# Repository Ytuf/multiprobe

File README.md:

# MultiProbe Pico Debugger :lemon:

# Description
A development board to debug multiple pico devices based on the official debug probe ( https://github.com/raspberrypi/debugprobe ) which does the following:
- 4 active SWD ports, debug four targets at once using a single usb/device.
- Extra indicator LEDs displays which port is active.
- 4 UARTS multiplexed to 2 CDC Com ports.
- Supports RP2040 & RP2350 based boards.

## Compatibility
Tested on the following platforms:
- Ubuntu 22.04
- Mac mini mac OS Sequoia 15.6.1
- Windows 10 *(requires driver workaround using zadig)*

## Installation
Install VSCode and the official Raspberry Pi Pico extension ( https://marketplace.visualstudio.com/items?itemName=raspberry-pi.raspberry-pi-pico )

## SWD target
To set the debug target use the "cmsis-dap usb interface" OpenOCD command which can be set in the vscode launch.json
```
"cmsis-dap usb interface 0",            // Use DEBUG 1 port
"cmsis-dap usb interface 1",            // Use DEBUG 2 port
"cmsis-dap usb interface 2",            // Use DEBUG 3 port
"cmsis-dap usb interface 3",            // Use DEBUG 4 port
```

## Example configurations
To debug all four targets with dual UARTs add the following launch config section to each VSCode project. 
Only 2 projects can have an active UART due to the limited number of UARTs on the RP2350 and pin assignments.

Debug project 1 with UART on COM port ACM0:
```
"openOCDLaunchCommands": [    
    "adapter speed 5000",
    "cmsis-dap usb interface 0",            // Use DEBUG 1 port
    "init",                
    "cmsis-dap cmd 0x81",                   // Use UART1 on ACM0   ( HWUart0 )
]
```

Debug project 2 with UART on COM port ACM1:
```
"openOCDLaunchCommands": [    
    "adapter speed 5000",
    "cmsis-dap usb interface 1",            // Use DEBUG 2 port
    "init",                
    "cmsis-dap cmd 0x92",                   // Use UART2 on ACM1   ( HWUart1 )
]
```

Debug project 3 with no UART
```
"openOCDLaunchCommands": [    
    "adapter speed 5000",
    "cmsis-dap usb interface 2",            // Use DEBUG 3 port    
]
```

Debug project 4 with no UART
```
"openOCDLaunchCommands": [    
    "adapter speed 5000",
    "cmsis-dap usb interface 3",            // Use DEBUG 4 port    
]
```

## Uart setup
There are only 2 UART devices available so 2 of the four UARTs must be routed, this defaults to UART1 -> ACM0, and UART2 -> ACM1. 
There are also some limitation on which UARTs can be used together as the RP2350 has hard limits on which pins the UART can be assigned.
he hardware UART must be different so for example UART1 and UART3 cannot be used at the same time, in that case you will have to swap the ports.
Future versions will use a PIO based UART which resolves this restriction and/or having 4 CDC devices (see limitation).

The UARTs must be assigned to a com port using the table below:

```
UART (silkscreen)   OpenOCD code    UART Device     Hardware UART
UART1               0x81            ACM0            HWUart0
UART2               0x82            ACM0            HWUart1
UART3               0x83            ACM0            HWUart0
UART4               0x84            ACM0            HWUart1
                            
UART1               0x91            ACM1            HWUart0
UART2               0x92            ACM1            HWUart1
UART3               0x93            ACM1            HWUart0
UART4               0x94            ACM1            HWUart1
```

**Hint**: The vendor code is formatted so the first digit (8 for ACM0 or 9 for ACM1) corresponds to the COM port and the last digit (1,2,3 & 4) is the 
UART number printed on the board silkscreen.

For example if you plug a device into UART4 and want to communicated on ACM1 you would enter  "cmsis-dap cmd 0x94". Some limitation apply due to the 
pico hardware UART can only be assigned to certain pins, for example UART1 and UART3 can't be used at the same time as they share the same RP2550 hardware 
device. In the future a PIO based UART will be used to allow any gpio assignment.

The probe uses vendor codes to setup the UART must be called after the OpenOCD "init" using the following command sequence set in the launch.json:

```
"openOCDLaunchCommands": [    
    "adapter speed 5000",
    "cmsis-dap usb interface 0",            // Use DEBUG 1 port
    "init",                
    "cmsis-dap cmd 0x81",                   // Use UART3 on ACM1   ( HWUart0 )
]
```

## Windows compatibility
Windows is not currently supported out the box as some workarounds are needed to function.

To enable multiple debug multiple instances of openOCD the windows driver needs replacing as the built in WinUSB will only allow a single process to access the usb device.
A utility called zadig ( https://zadig.akeo.ie/ ) can replace the driver to allow multiple openOCD instances.

Warning: This can break your system if you select the wrong device, ensure the DAP device is selected before clicking the install button.
- Plug in the debugger into a USB port.
- download and run Zadig-2.9.exe from https://zadig.akeo.ie/ and click "Yes" on the UAC permission prompt.
- Go Options -> List All Devices
- The Device list will be populated and should have 4 CMSIS-DAP devices.
- Select "CMSIS-DAP v2 Interface (Interface 0)
- The driver input on the left should read "WinUSB", change the value on the right ( after the arrow ) to "libusbK" eg. WinUSB -> libusbK.
- Click "Install driver"
- Repeat for all 4 interfaces eg. "CMSIS-DAP v2 Interface (Interface 0), "CMSIS-DAP v2 Interface (Interface 1), "CMSIS-DAP v2 Interface (Interface 2) 
and "CMSIS-DAP v2 Interface (Interface 3)
- Reboot if needed

## Hacking
Open the project in VSCode using the "Raspberry Pi Pico" extension and compile.

## Changes from debugprobe
- VSCode based project
- hacked in multiple UARTs
- hacked in multiple port PIO DAP interfaces

## Testing
Connect a pico device to each port of the debug probe then open "testing/blink_iface0", "testing/blink_iface1", "testing/blink_iface2" and "testing/blink_iface3" 
in separate windows, Hit F5 to debug each to verify the openOCD debugger works in parallel. 

## Todo
- Fork official repo ( https://github.com/raspberrypi/debugprobe ) and make it easier to integrate upstream changes.
- PIO based UART to allow any gpio assignment and 4 active uarts without the vendor command routing.
- Resolve the 2 CDC device limit in usb descriptors/tinyusb configuration.

## Building your own
Any RP2040 or RP2350 device can be used, see multiprobe-pcb.kicad_sch for the gpio assignments or order a pcb from your favorite pcb supplier by submitting the 
hw/multiprobe-pcb/production/* files. A purchasable board is also available on tindie (https://www.tindie.com/products/picolemon/multiprobe-pico-debugger/).

### Support :zap:
- Email help@picolemon.com

Copyright (c) 2025 picoLemon

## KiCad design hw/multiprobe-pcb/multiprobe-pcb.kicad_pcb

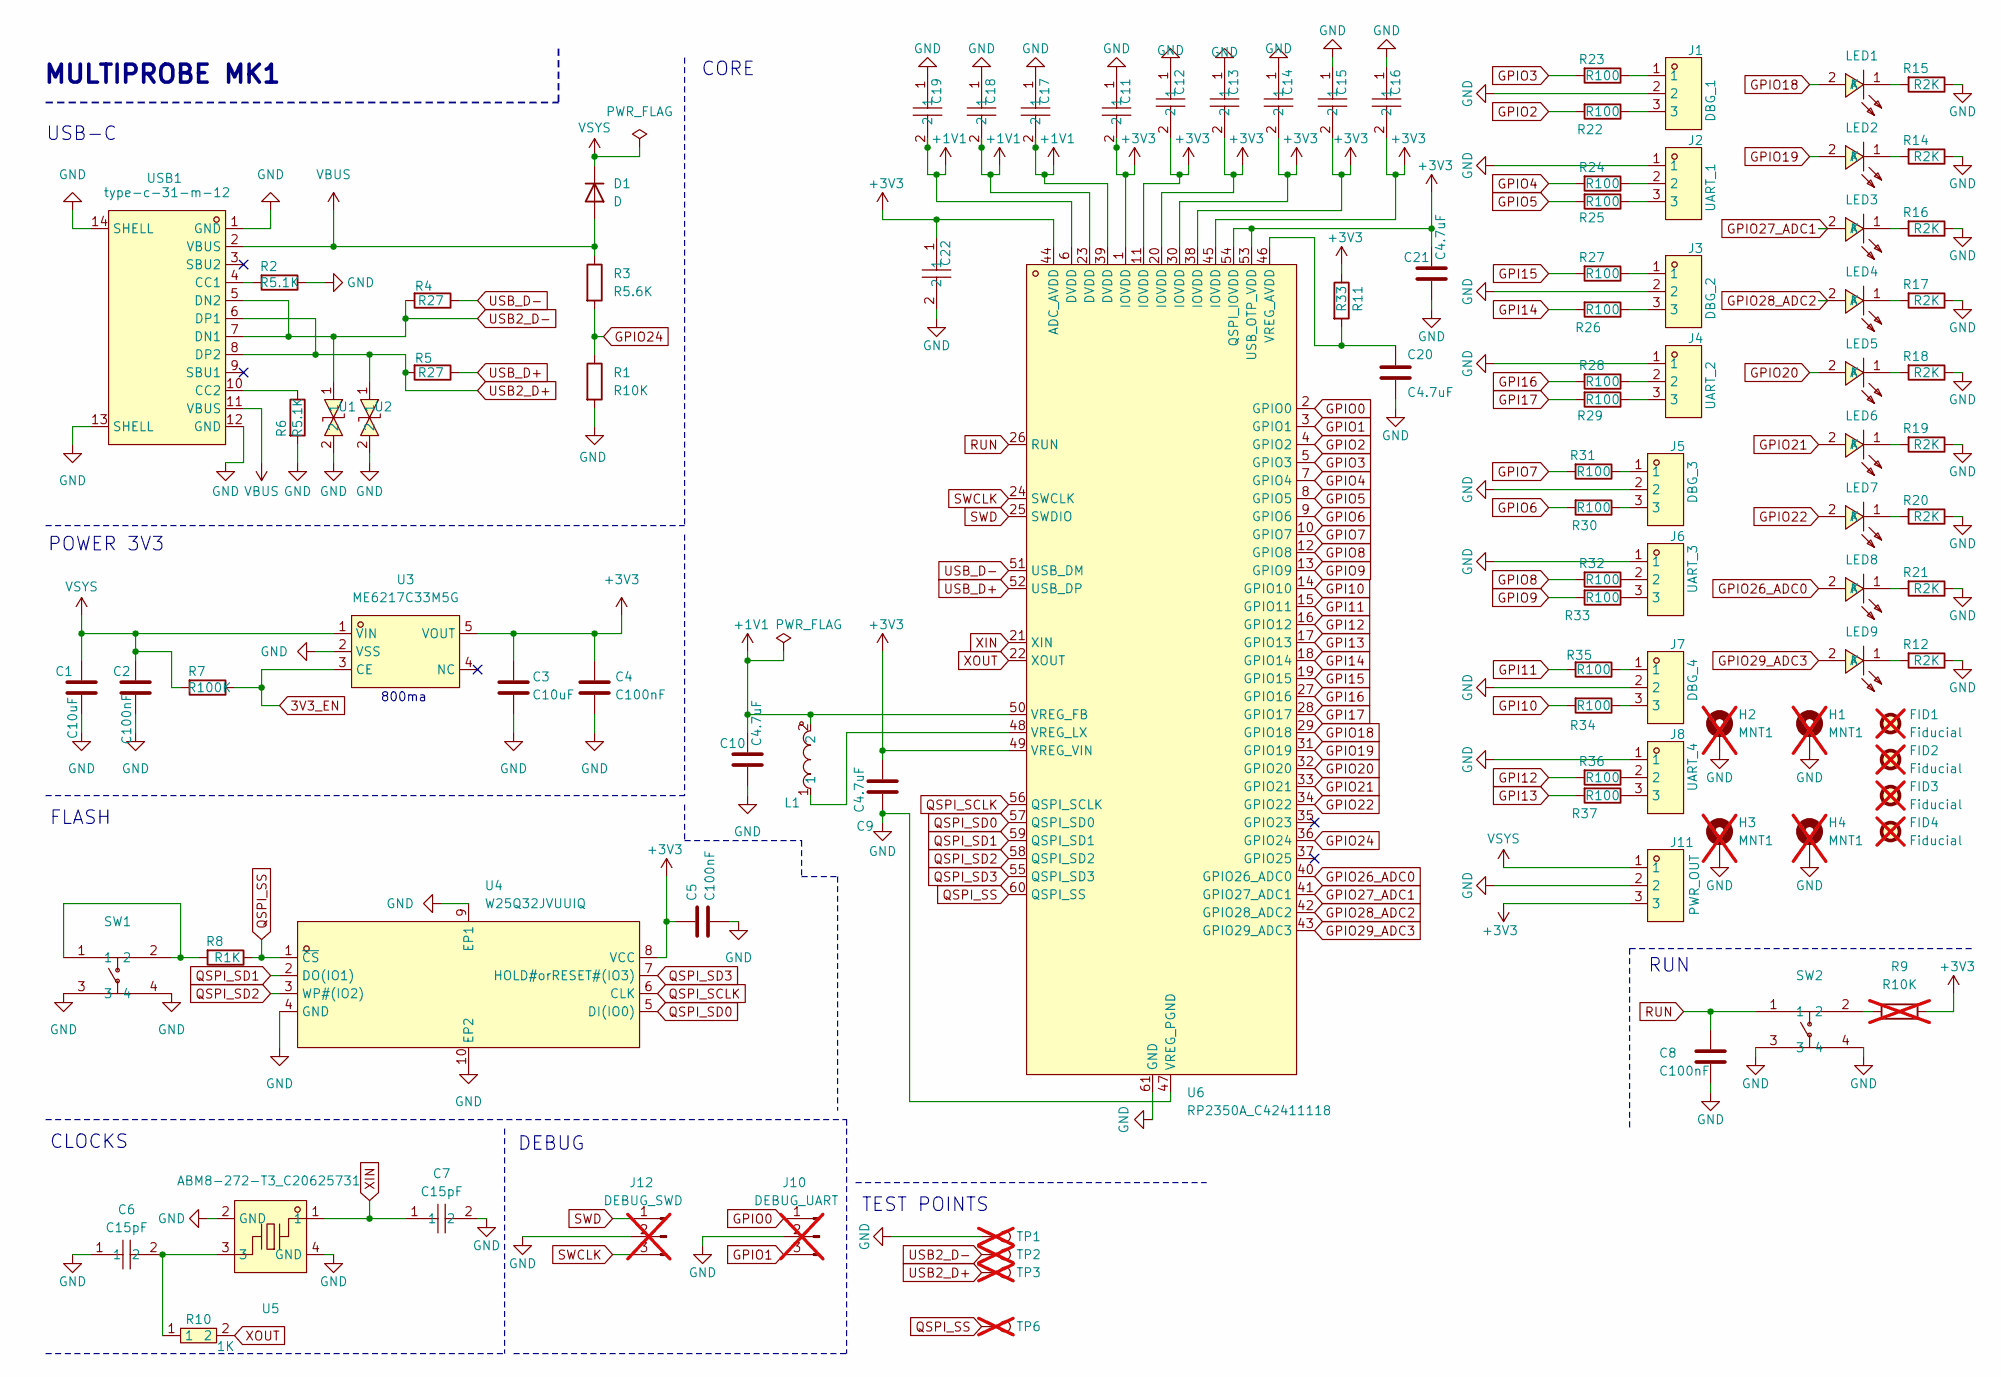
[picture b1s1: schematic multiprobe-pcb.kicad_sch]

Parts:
C1, C3: C10uF; C0402; LCSC Part C77000
C2, C4, C5, C8: C100nF; C0402; LCSC Part C77020
C6, C7: C15pF; C0402; LCSC Part C140684
C9, C10, C21: C4.7uF; C_0402_1005Metric; LCSC Part C368809
C11, C12, C13, C14, C15, C16, C17, C18, C19, C22: 100nf; C0402; LCSC Part C1525
C20: C4.7uF; C0402; LCSC Part C368809
D1: D; POWERDI-123_L2.8-W1.8-LS3.7-RD; LCSC Part C110493
FID1, FID2, FID3, FID4: Fiducial; Fiducial_1mm_Mask2mm; not fitted
H1, H2, H3, H4: MNT1; MountingHole_2.2mm_M2_DIN965_Pad; not fitted
J1: DBG_1; HDR-TH_3P-P2.54-H-M-BW7.2-P; LCSC Part C92159
J2: UART_1; HDR-TH_3P-P2.54-H-M-BW7.2-P; LCSC Part C92159
J3: DBG_2; HDR-TH_3P-P2.54-H-M-BW7.2-P; LCSC Part C92159
J4: UART_2; HDR-TH_3P-P2.54-H-M-BW7.2-P; LCSC Part C92159
J5: DBG_3; HDR-TH_3P-P2.54-H-M-BW7.2-P; LCSC Part C92159
J6: UART_3; HDR-TH_3P-P2.54-H-M-BW7.2-P; LCSC Part C92159
J7: DBG_4; HDR-TH_3P-P2.54-H-M-BW7.2-P; LCSC Part C92159
J8: UART_4; HDR-TH_3P-P2.54-H-M-BW7.2-P; LCSC Part C92159
J10: DEBUG_UART; PinHeader_1x03_P2.54mm_Vertical; not fitted
J11: PWR_OUT; HDR-TH_3P-P2.54-H-M-BW7.2-P; LCSC Part C92159
J12: DEBUG_SWD; PinHeader_1x03_P2.54mm_Vertical; not fitted
L1: AOTA-B201610S3R3-101-T; IND-SMD_L2.0-W1.6_AOTA-B201610S3R3-101-T; LCSC Part C42411119
LED1, LED2, LED3, LED4, LED5, LED6, LED7, LED8: LED0402-RD; LCSC Part C130723
LED9: LED0402-RD; LCSC Part C130719
R1: R10K; R0402; LCSC Part C60490
R2, R6: R5.1K; R0402; LCSC Part C25941
R3: R5.6K; R0402; LCSC Part C25908
R4, R5: R27; R0402; LCSC Part C25100
R7: R100K; R0402; LCSC Part C60491
R8: R1K; R0402; LCSC Part C25543
R9: R10K; R0402; LCSC Part C60490; not fitted
R10: 1K; R0402; LCSC Part C11702
R11: R33; R0402; LCSC Part C852729
R12, R14, R15, R16, R17, R18, R19, R20, R21: R2K; R0402; LCSC Part C4109
R22, R23, R24, R25, R26, R27, R28, R29, R30, R31, R32, R33, R34, R35, R36, R37: R100; R0402; LCSC Part C25076
SW1, SW2: KEY-SMD_4P-L4.2-W3.2-P2.20-LS5.1-TL; LCSC Part C92589
TP1, TP2, TP3, TP6: TestPoint_Pad_D1.0mm; not fitted
U1, U2: RCLAMP0521P.TCT_C3029033; D0402-BI; LCSC Part C3029033
U3: ME6217C33M5G; SOT-23-5_L3.0-W1.7-P0.95-LS2.8-BR; LCSC Part C427602
U4: W25Q32JVUUIQ; USON-8_L4.0-W3.0-P0.80-BL_WINBOND_UU; LCSC Part C2999380
U5: ABM8-272-T3_C20625731; CRYSTAL-SMD_4P-L3.2-W2.5-BL; LCSC Part C20625731
U6: RP2350A_C42411118; QFN-60_L7.0-W7.0-P0.40-TL-EP3.4; LCSC Part C42411118
USB1: type-c-31-m-12; USB-C-SMD_TYPE-C-6PIN-2MD-073; LCSC Part C2765186

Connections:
3V3_EN: R7.1, U3.3 (CE)
+1V1: C10.1, C17.2, C18.2, C19.2, L1.2, U6.6 (DVDD), U6.23 (DVDD), U6.39 (DVDD), U6.50 (VREG_FB)
+3V3: C3.1, C4.1, C5.1, C9.1, C11.2, C12.2, C13.2, C14.2, C15.2, C16.2, C21.1, C22.1, J11.3, R9.2, R11.1, U3.5 (VOUT), U4.8 (VCC), U6.1 (IOVDD), U6.11 (IOVDD), U6.20 (IOVDD), U6.30 (IOVDD), U6.38 (IOVDD), U6.44 (ADC_AVDD), U6.45 (IOVDD), U6.49 (VREG_VIN), U6.53 (USB_OTP_VDD), U6.54 (QSPI_IOVDD)
GND: C1.2, C2.2, C3.2, C4.2, C5.2, C6.1, C7.2, C8.2, C9.2, C10.2, C11.1, C12.1, C13.1, C14.1, C15.1, C16.1, C17.1, C18.1, C19.1, C20.2, C21.2, C22.2, H1.1, H2.1, H3.1, H4.1, J1.2, J2.1, J3.2, J4.1, J5.2, J6.1, J7.2, J8.1, J10.2, J11.2, J12.2, R1.2, R2.1, R6.2, R12.1, R14.1, R15.1, R16.1, R17.1, R18.1, R19.1, R20.1, R21.1, SW1.3, SW1.4, SW2.3, SW2.4, TP1.1, U1.2, U2.2, U3.2 (VSS), U4.4 (GND), U4.9 (EP1), U4.10 (EP2), U5.2 (GND), U5.4 (GND), U6.47 (VREG_PGND), U6.61 (GND), USB1.1 (GND), USB1.12 (GND), USB1.13 (SHELL), USB1.14 (SHELL)
GPI10: R34.2, U6.14 (GPIO10)
GPI11: R35.2, U6.15 (GPIO11)
GPI12: R36.2, U6.16 (GPIO12)
GPI13: R37.2, U6.17 (GPIO13)
GPI14: R26.2, U6.18 (GPIO14)
GPI15: R27.2, U6.19 (GPIO15)
GPI16: R28.2, U6.27 (GPIO16)
GPI17: R29.2, U6.28 (GPIO17)
GPIO0: J10.1, U6.2 (GPIO0)
GPIO1: J10.3, U6.3 (GPIO1)
GPIO2: R22.2, U6.4 (GPIO2)
GPIO3: R23.2, U6.5 (GPIO3)
GPIO4: R24.2, U6.7 (GPIO4)
GPIO5: R25.2, U6.8 (GPIO5)
GPIO6: R30.2, U6.9 (GPIO6)
GPIO7: R31.2, U6.10 (GPIO7)
GPIO8: R32.2, U6.12 (GPIO8)
GPIO9: R33.2, U6.13 (GPIO9)
GPIO18: LED1.2 (A), U6.29 (GPIO18)
GPIO19: LED2.2 (A), U6.31 (GPIO19)
GPIO20: LED5.2 (A), U6.32 (GPIO20)
GPIO21: LED6.2 (A), U6.33 (GPIO21)
GPIO22: LED7.2 (A), U6.34 (GPIO22)
GPIO24: R1.1, R3.2, U6.36 (GPIO24)
GPIO26_ADC0: LED8.2 (A), U6.40 (GPIO26_ADC0)
GPIO27_ADC1: LED3.2 (A), U6.41 (GPIO27_ADC1)
GPIO28_ADC2: LED4.2 (A), U6.42 (GPIO28_ADC2)
GPIO29_ADC3: LED9.2 (A), U6.43 (GPIO29_ADC3)
unnamed: C6.2, R10.1, U5.3
unnamed: J1.1, R23.1
unnamed: J1.3, R22.1
unnamed: J2.2, R24.1
unnamed: J2.3, R25.1
unnamed: J3.1, R27.1
unnamed: J3.3, R26.1
unnamed: J4.2, R28.1
unnamed: J4.3, R29.1
unnamed: J5.1, R31.1
unnamed: J5.3, R30.1
unnamed: J6.2, R32.1
unnamed: J6.3, R33.1
unnamed: J7.1, R35.1
unnamed: J7.3, R34.1
unnamed: J8.2, R36.1
unnamed: J8.3, R37.1
unnamed: LED1.1 (K), R15.2
unnamed: LED2.1 (K), R14.2
unnamed: LED3.1 (K), R16.2
unnamed: LED4.1 (K), R17.2
unnamed: LED5.1 (K), R18.2
unnamed: LED6.1 (K), R19.2
unnamed: LED7.1 (K), R20.2
unnamed: LED8.1 (K), R21.2
unnamed: LED9.1 (K), R12.2
unnamed: R8.2, SW1.1, SW1.2
unnamed: R9.1, SW2.2
unnamed: C20.1, R11.2, U6.46 (VREG_AVDD)
unnamed: L1.1, U6.48 (VREG_LX)
unnamed: R2.2, USB1.4 (CC1)
unnamed: R6.1, USB1.10 (CC2)
QSPI_SCLK: U4.6 (CLK), U6.56 (QSPI_SCLK)
QSPI_SD0: U4.5 (DI(IO0)), U6.57 (QSPI_SD0)
QSPI_SD1: U4.2 (DO(IO1)), U6.59 (QSPI_SD1)
QSPI_SD2: U4.3 (WP#(IO2)), U6.58 (QSPI_SD2)
QSPI_SD3: U4.7 (HOLD#orRESET#(IO3)), U6.55 (QSPI_SD3)
QSPI_SS: R8.1, TP6.1, U4.1 (~CS), U6.60 (QSPI_SS)
RUN: C8.1, SW2.1, U6.26 (RUN)
SWCLK: J12.3, U6.24 (SWCLK)
SWD: J12.1, U6.25 (SWDIO)
USB2_D+: R5.2, TP3.1, U2.1, USB1.6 (DP1), USB1.8 (DP2)
USB2_D-: R4.2, TP2.1, U1.1, USB1.5 (DN2), USB1.7 (DN1)
USB_D+: R5.1, U6.52 (USB_DP)
USB_D-: R4.1, U6.51 (USB_DM)
VBUS: D1.2 (A), R3.1, USB1.2 (VBUS), USB1.11 (VBUS)
VSYS: C1.1, C2.1, D1.1 (K), J11.1, R7.2, U3.1 (VIN)
XIN: C7.1, U5.1, U6.21 (XIN)
XOUT: R10.2, U6.22 (XOUT)

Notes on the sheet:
RUN
USB-C
800ma
POWER 3V3
TEST POINTS
CLOCKS
CORE
MULTIPROBE MK1
DEBUG
FLASH

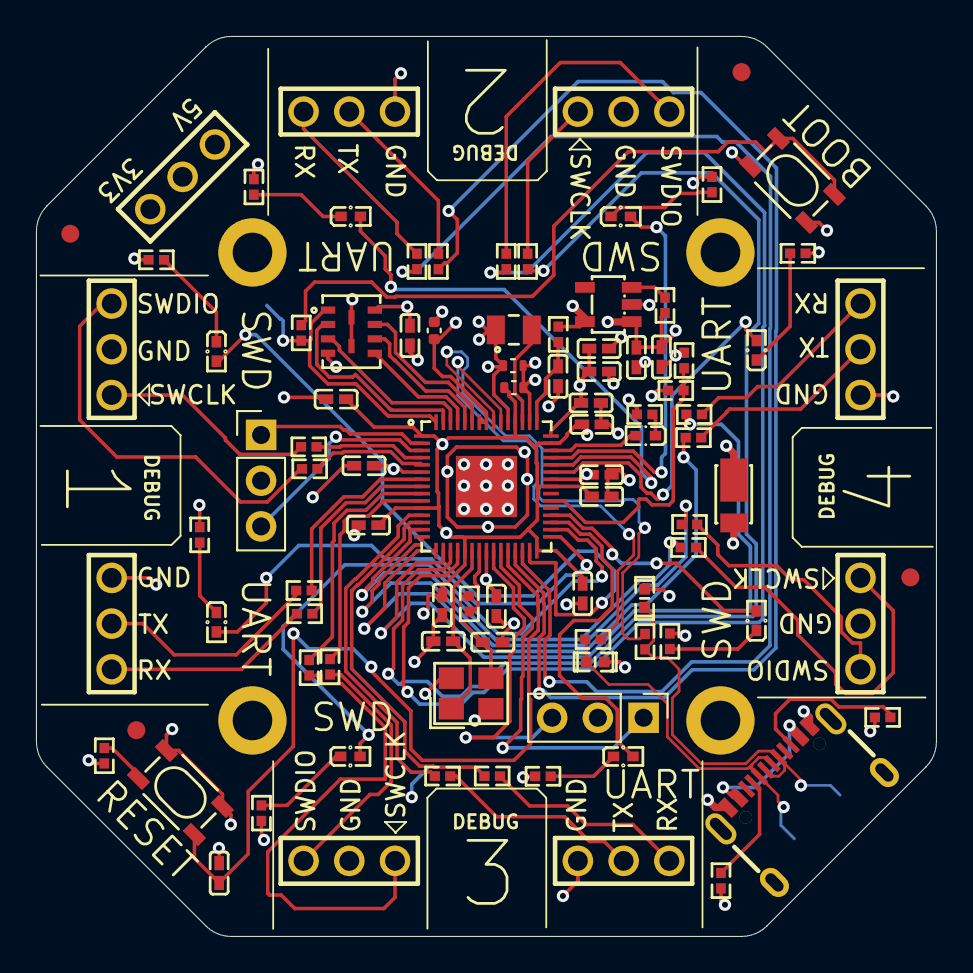
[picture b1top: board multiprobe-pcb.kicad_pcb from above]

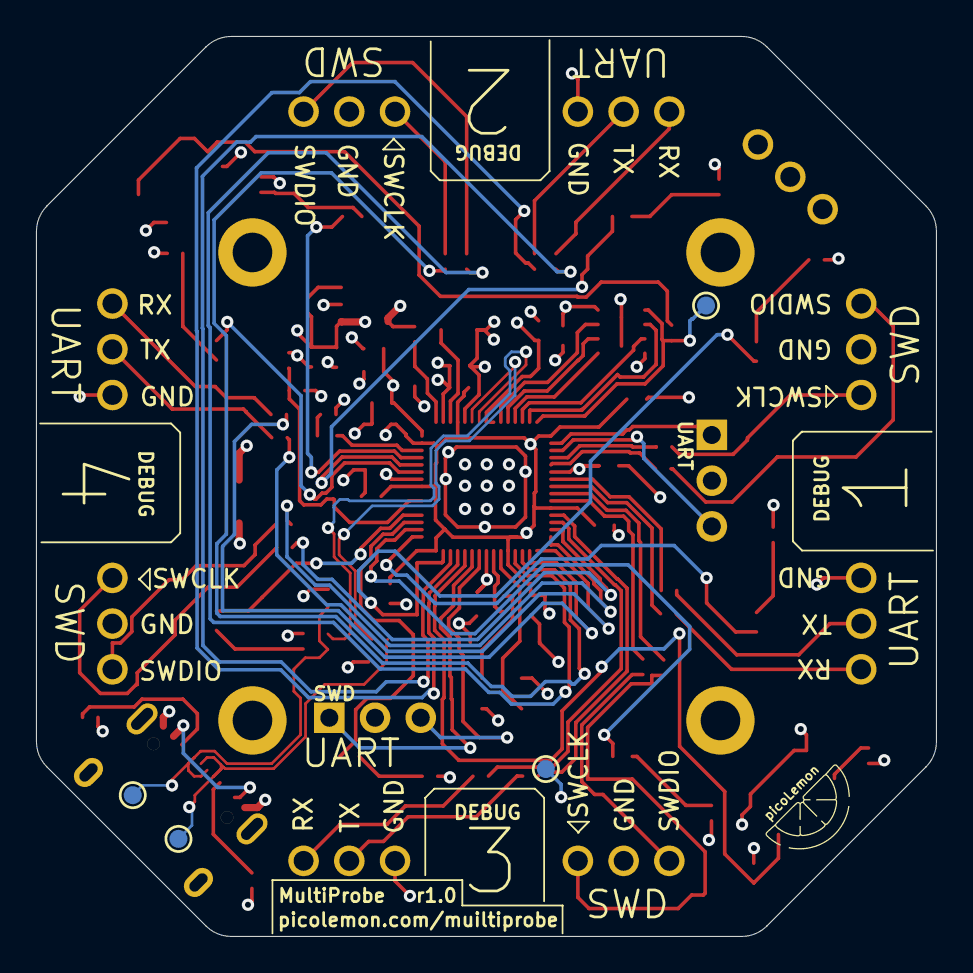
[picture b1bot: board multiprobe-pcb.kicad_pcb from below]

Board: 4 copper layers, 50.0 x 50.0 mm, 101 parts (4 on the bottom side), 81 nets.

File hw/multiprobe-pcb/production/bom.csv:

Designator,Footprint,Quantity,Value,LCSC Part #
"C1, C3",C0402,2,C10uF,C77000
"C10, C21, C9",0402,3,C4.7uF,C368809
"C11, C12, C13, C14, C15, C16, C17, C18, C19, C22",C0402,10,100nf,C1525
"C2, C4, C5, C8",C0402,4,C100nF,C77020
C20,C0402,1,C4.7uF,C368809
"C6, C7",C0402,2,C15pF,C140684
D1,POWERDI-123_L2.8-W1.8-LS3.7-RD,1,D,C110493
J1,HDR-TH_3P-P2.54-H-M-BW7.2-P,1,DBG_1,C92159
J11,HDR-TH_3P-P2.54-H-M-BW7.2-P,1,PWR_OUT,C92159
J2,HDR-TH_3P-P2.54-H-M-BW7.2-P,1,UART_1,C92159
J3,HDR-TH_3P-P2.54-H-M-BW7.2-P,1,DBG_2,C92159
J4,HDR-TH_3P-P2.54-H-M-BW7.2-P,1,UART_2,C92159
J5,HDR-TH_3P-P2.54-H-M-BW7.2-P,1,DBG_3,C92159
J6,HDR-TH_3P-P2.54-H-M-BW7.2-P,1,UART_3,C92159
J7,HDR-TH_3P-P2.54-H-M-BW7.2-P,1,DBG_4,C92159
J8,HDR-TH_3P-P2.54-H-M-BW7.2-P,1,UART_4,C92159
L1,IND-SMD_L2.0-W1.6_AOTA-B201610S3R3-101-T,1,AOTA-B201610S3R3-101-T,C42411119
"LED1, LED2, LED3, LED4, LED5, LED6, LED7, LED8",LED0402-RD,8,~,C130723
LED9,LED0402-RD,1,~,C130719
R1,R0402,1,R10K,C60490
R10,R0402,1,1K,C11702
R11,R0402,1,R33,C852729
"R12, R14, R15, R16, R17, R18, R19, R20, R21",R0402,9,R2K,C4109
"R2, R6",R0402,2,R5.1K,C25941
"R22, R23, R24, R25, R26, R27, R28, R29, R30, R31, R32, R33, R34, R35, R36, R37",R0402,16,R100,C25076
R3,R0402,1,R5.6K,C25908
"R4, R5",R0402,2,R27,C25100
R7,R0402,1,R100K,C60491
R8,R0402,1,R1K,C25543
"SW1, SW2",KEY-SMD_4P-L4.2-W3.2-P2.20-LS5.1-TL,2,~,C92589
"U1, U2",D0402-BI,2,RCLAMP0521P.TCT_C3029033,C3029033
U3,SOT-23-5_L3.0-W1.7-P0.95-LS2.8-BR,1,ME6217C33M5G,C427602
U4,USON-8_L4.0-W3.0-P0.80-BL_WINBOND_UU,1,W25Q32JVUUIQ,C2999380
U5,CRYSTAL-SMD_4P-L3.2-W2.5-BL,1,ABM8-272-T3_C20625731,C20625731
U6,QFN-60_L7.0-W7.0-P0.40-TL-EP3.4,1,RP2350A_C42411118,C42411118
USB1,USB-C-SMD_TYPE-C-6PIN-2MD-073,1,type-c-31-m-12,C2765186

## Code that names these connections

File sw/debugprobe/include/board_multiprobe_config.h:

/*
 * The MIT License (MIT)
 *
 * Copyright (c) 2025 Picolemon
 *
 * Permission is hereby granted, free of charge, to any person obtaining a copy
 * of this software and associated documentation files (the "Software"), to deal
 * in the Software without restriction, including without limitation the rights
 * to use, copy, modify, merge, publish, distribute, sublicense, and/or sell
 * copies of the Software, and to permit persons to whom the Software is
 * furnished to do so, subject to the following conditions:
 *
 * The above copyright notice and this permission notice shall be included in
 * all copies or substantial portions of the Software.
 *
 * THE SOFTWARE IS PROVIDED "AS IS", WITHOUT WARRANTY OF ANY KIND, EXPRESS OR
 * IMPLIED, INCLUDING BUT NOT LIMITED TO THE WARRANTIES OF MERCHANTABILITY,
 * FITNESS FOR A PARTICULAR PURPOSE AND NONINFRINGEMENT. IN NO EVENT SHALL THE
 * AUTHORS OR COPYRIGHT HOLDERS BE LIABLE FOR ANY CLAIM, DAMAGES OR OTHER
 * LIABILITY, WHETHER IN AN ACTION OF CONTRACT, TORT OR OTHERWISE, ARISING FROM,
 * OUT OF OR IN CONNECTION WITH THE SOFTWARE OR THE USE OR OTHER DEALINGS IN
 * THE SOFTWARE.
 *
 */

#ifndef BOARD_MULTIPROBE_H_
#define BOARD_MULTIPROBE_H_

#define PROBE_IO_RAW
#define PROBE_CDC_UART

// ---------------------------------------------------------------------------
// FreeWili pin map (RP2350B)
// ---------------------------------------------------------------------------
// External PROM EEPROMs on I2C
#define PROM_I2C_SDA_PIN     0       // I2C0 SDA -> PROM
#define PROM_I2C_SCL_PIN     1       // I2C0 SCL -> PROM
#define PROM_I2C_INSTANCE    i2c0
#define PROM1_I2C_SDA_PIN    18      // I2C1 SDA -> PROM1
#define PROM1_I2C_SCL_PIN    19      // I2C1 SCL -> PROM1
#define PROM1_I2C_INSTANCE   i2c1

// Status / indicator LEDs
#define BOARD_LED_PIN        2       // Driven high at boot (steady on)
#define SWD_READY_LED_PIN    15      // Green: any SWD probe connected (initted)
#define SWD_ACT_LED_PIN      16      // Yellow: SWD transaction recently observed

// PIC ICSP master clear pull line
// Configured as input with internal pull-up: idles high, not actively driven.
// TODO: revisit if/when MCLR_PULL needs to be driven (e.g., to assert reset).
#define PIC_MCLR_PULL_PIN    3

// TODO: GPIO4/5 are wired to PIC16 ICSPDAT/ICSPCLK. They are currently
//       configured as UART1 (UART_CONFIG0 / "PIC" profile). Verify that the
//       PIC firmware actually exposes a UART on these pins -- if it's pure
//       ICSP we'll need a different driver, not the CDC-UART path.

// ---------------------------------------------------------------------------

// UART config - FreeWili: GPIO4/5 is PIC UART (TBD - see note above), keep UART1 for that; disable others to avoid SWD pin conflicts
#define UART_CONFIG0 { .index=0, .name="PIC", .txPin=4, .rxPin=5, .hwUartId=1, .baud=115200, .activityLedPin=-1 }           // PIC16 UART/ICSP (GPIO4/5) - confirm
#define UART_CONFIG1 { .index=1, .name="UNUSED1", .txPin=-1, .rxPin=-1, .hwUartId=0, .baud=115200, .activityLedPin=-1 }     // Disabled - pins used for SWD
#define UART_CONFIG2 { .index=2, .name="UNUSED2", .txPin=-1, .rxPin=-1, .hwUartId=1, .baud=115200, .activityLedPin=-1 }     // Disabled - pins used for SWD
#define UART_CONFIG3 { .index=3, .name="UNUSED3", .txPin=-1, .rxPin=-1, .hwUartId=0, .baud=115200, .activityLedPin=-1 }     // Disabled

// SWD probe config - FreeWili RP2040 debug processor pin assignments
#define PROBE_CONFIG0 {.name="DISPLAY", .pio=pio0, .sm=0, .clkPin=10, .dioPin=11, .activityLedPin=-1}                       // Display RP2350B
#define PROBE_CONFIG1 {.name="MAIN",    .pio=pio0, .sm=1, .clkPin=12, .dioPin=13, .activityLedPin=-1}                       // Main RP2350B (GPIO14 tied to GPIO13 externally; left at default input/no-pull)
#define PROBE_CONFIG2 {.name="WIO-E5",  .pio=pio1, .sm=0, .clkPin=9,  .dioPin=8,  .activityLedPin=-1}                       // STM32WLE5JC
#define PROBE_CONFIG3 {.name="UNUSED",  .pio=pio1, .sm=1, .clkPin=-1, .dioPin=-1, .activityLedPin=-1}                       // Disabled

// #define PROBE_USB_CONNECTED_LED -1  // FreeWili: no dedicated USB LED

#define PROBE_PRODUCT_STRING "FreeWili Debug Probe (CMSIS-DAP)"

#endif

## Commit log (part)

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2025-09-10 Initial release
